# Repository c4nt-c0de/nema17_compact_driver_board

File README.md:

# Wi-Fi-Controlled Stepper Motor Driver Board

As part of an embedded programming coursework, I designed a custom compact Wi-Fi-controlled stepper motor driver board engineered to mount directly onto the back of a NEMA17 motor.

Before the design phase, we were required to submit an initial project proposal (this file is in the "study" folder). As always, there were some deviations from that plan due to unexpected challenges and poor decisions.

---

## Hardware Overview

* Microcontroller: ESP32-S2-MINI-2-N4
* Stepper Driver: TMC2209-LA-T (featuring UART interface for stallGuard and configuration)
* Shaft Encoder: AS5600-ASOT
* IR Receiver: IRM-H638T-TR2-TL
* Power Supply: 
  * Motor Power: RJ45 connector (testing whether a Cat5 cable can be used to supply power to the motor over a longer distance than a typical USB cable)
  * Logic Power: USB-C (5V) using a TPS54331DR switching regulator

---

## Board Renders & Layout

The biggest experiment in this project was attempting to place components on both sides of the PCB. At the time of design, JLCPCB did not offer double-sided PCBA services. While the cost today would likely deter me from this approach, I needed to populate both sides to fit the design onto the back of a NEMA17 motor.

I opted for a standard PCBA with components soldered to the top side, but the board was designed to be cut in half, with the two sections then glued together and soldered at specific points to create electrical connections.

The choice of an RJ45 connector for delivering power was also unconventional, but it was on hand and, by my calculations, could safely carry 24V at the expected currents.

### Top View

### Bottom View

### Front Layout

---

## Schematics & Subsystems

### Complete System Schematic

<br><br>
### Power Connector

<br><br>
### Switching Regulator (TPS54331DR)

<br><br>
### Stepper Driver (TMC2209)

<br><br>
### Shaft Encoder (AS5600)

<br><br>
### IR Receiver (IRM-H630T)

<br><br>
### External Crystal

---

## Firmware & Logic

The firmware runs on the ESP32-S2, handling:
1. Motor Control: Managed via stepper driver libraries (e.g., [TMCStepper](https://github.com/teemuatlut/TMCStepper)).
2. Position Tracking: Sampling PWM output from the AS5600 magnetic encoder.
3. Communication: Receiving motion commands over Wi-Fi via a simple web GUI and transmitting real-time shaft position and StallGuard values.

---

## Retrospective & Mistakes

This project would require a few more iterations to be considered a full success, but it was a significant learning experience. I improved my soldering skills by necessity, having to remove components and bridge pads with wire to correct design errors. I also hand-soldered the ESP32 module, something I had never done before, because JLCPCB was out of stock on the module I was already familiar with.

The motor successfully spun based on commands, counted steps, tracked shaft position, and returned StallGuard values. However, torque was limited and mechanical assembly was tedious.

* **Double-sided PCB:** Sticking together two PCBs seemed interesting, but caused many headaches. Even designing it in KiCad was far more difficult than expected, and the final assembly was tedious. I wouldn't repeat it unless absolutely necessary, though it does save space. If I ever attempt something similar, I should design the through-holes large enough to accommodate a typical Arduino pin that can be pushed through and soldered from both sides to create a crude via. My through-holes were too small, making it difficult for solder to flow into the tight spaces.

* **The Logic Voltage Drop:** A major oversight involved the reverse current protection on the 5V rail near the USB-C port. The diode introduced an excessive voltage drop that dragged the voltage too far below 5V when powered exclusively via USB-C, completely preventing the TMC2209 drivers from functioning until I physically bypassed the diode and shorted the pads. Consequently, I relied entirely on 5V from the USB port, which limited motor torque significantly.

Every mistake taught me far more about board bring-up and power distribution than a flawless design would have. Ultimately, I am satisfied with the result: I learned a great deal, completed an independent project, and passed the class.

## Photos of the Assembled Board
<div align="center">
  <table>
    <tr>
      <td align="center"><b>Corner View</b></td>
      <td align="center"><b>Top View</b></td>
    </tr>
    <tr>
      <td align="center" style="padding: 10px;">
        
      </td>
      <td align="center" style="padding: 10px;">
        
      </td>
    </tr>
  </table>
</div>

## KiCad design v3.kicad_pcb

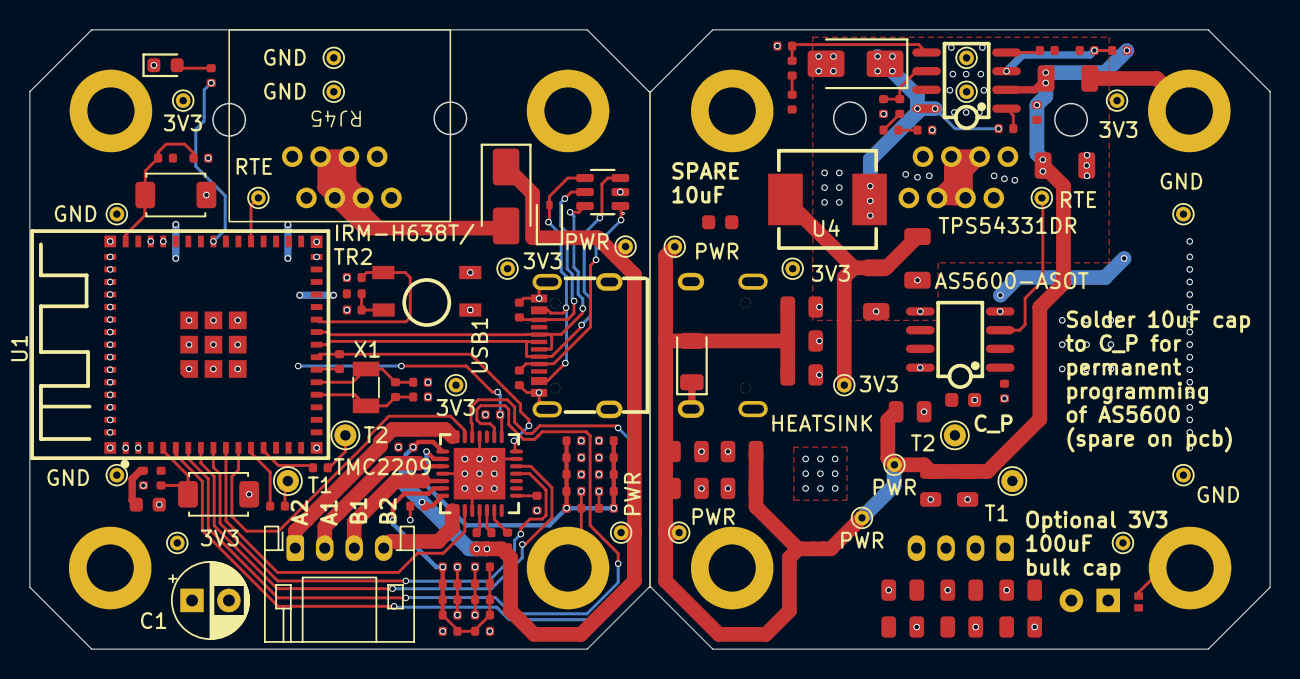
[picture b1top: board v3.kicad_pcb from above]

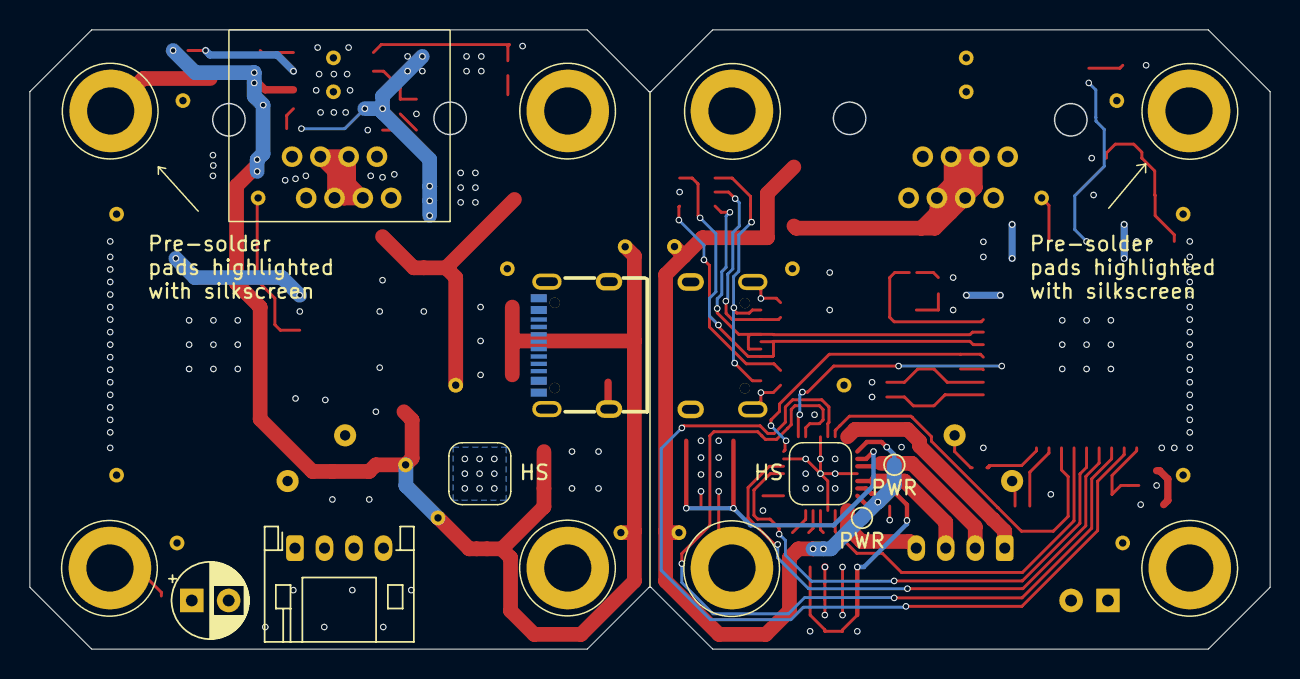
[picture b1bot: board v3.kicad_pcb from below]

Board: 2 copper layers, 84.1 x 42.0 mm, 140 parts (10 on the bottom side), 49 nets.

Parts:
BOOT1: Tactile Button, 160gf; SW_TS-1088-AR02016
C1, C1#2: C_Polarized; CP_Radial_D5.0mm_P2.50mm
C2, C4, C6, C7, C8, C9: 22uF; C_0805
C3: 22uF; C_0603
C5, C10, C11, C20, C25, C27, C28, C29: 100nF; C_0402
C12, C13: 10uF; C_0603
C14, C15: 4.7uF; C_1206
C16, C17: 10nF; C_0402
C18: 47pF; C_0402
C19: 1nF; C_0402
C21, C22: 47uF; C_1206
C23: 4.7uF; C_0402
C24: 2.2uF; C_0402
C26: 22nF; C_0402
C30, C31, C32, C33, C34, C35, C36, C37, C38, C39: 10uF; C_0805
C40, C41: 12pF; C_0402
CGQ1: IRM-H638T/TR2; SENSOR-SMD_IRM-H638T-TR2-TL
D1: SRV05-4_C7420376; SOT-23-6_L2.9-W1.6-P0.95-LS2.8-BL-1
D2: 1N5819WS; D_SOD-323
D3: SS54; D_SMA
D4: Red; D_0603
D5: SMF24CA; D_SOD-123FL
D6: H3V3L10B; D_DFN1006-2L
D7: SSL34; D_SMA
H1, H1#2, H2, H2#2, H3, H3#2, H4, H4#2: MountingHole_Pad; MountingHole_3.2mm_M3_DIN965_Pad
J1, J1#2: RJ45; RJ45_home
J2, J2#2: Conn_01x04_Socket; JST_PH_S4B-PH-K_1x04_P2.00mm_Horizontal
R1, R2: 5.1kΩ; R_0402
R3, R8, R14: 10kΩ; R_0402
R4, R5, R6: 1kΩ; R_0402
R7: 330Ω; R_0402
R9: 330kΩ; R_0402
R10, R16: 100kΩ; R_0402
R11: 2.4kΩ; R_0402
R12: 27kΩ; R_0402
R13: 3.3kΩ; R_0402
R15: 0Ω; R_0402
R17: 100Ω; R_0402
R18, R19, R20, R21, R22, R23, R24, R25, R26, R27, R28, R29, R30, R31, R32, R33, R34, R35, R36, R37: 1Ω; R_0402
R38: 1MΩ; R_0402
RST1: Tactile Button, 160gf; SW_TS-1088-AR02016
TP1, TP1#2, TP2, TP2#2, TP3, TP3#3, TP4#2, TP4#3: GND; TestPoint_THTPad_D1.0mm_Drill0.5mm
TP2#3, TP6, TP6#3, TP6#4, TP7#2, TP8: PWR; TestPoint_THTPad_D1.0mm_Drill0.5mm
TP3#2, TP5: T1; TestPoint_THTPad_D1.5mm_Drill0.7mm
TP4, TP6#2: T2; TestPoint_THTPad_D1.5mm_Drill0.7mm
TP7, TP10#2: RTE; TestPoint_THTPad_D1.0mm_Drill0.5mm
TP9, TP11#2: PWR; TestPoint_Pad_D1.0mm
TP10, TP11, TP12, TP12#2, TP13, TP13#2, TP14, TP15: 3V3; TestPoint_THTPad_D1.0mm_Drill0.5mm
U1: 2.4GHz; ESP32-S2-MINI-2-N4
U2: AS5600-ASOT; SOIC-8_L5.0-W4.0-P1.27-LS6.0-BL
U3: TPS54331DR; SOIC-8_L5.0-W4.0-P1.27-LS6.0-BL
U4: CYA0630-6.8UH; IND-SMD_L7.2-W6.6_GPSR0730
U5: TMC2209-LA-T; QFN-28_L5.0-W5.0-P0.50-BL-EP
USB1, USB1#2: TYPE-C 16PIN 2MD(073); USB-C-SMD_TYPE-C-6PIN-2MD-073
X1: Q13FC1350000400; Crystal_SMD_3215-2Pin_3.2x1.5mm

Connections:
3V3: C1.1, C1#2.1, C2.2, C3.1, C4.2, C5.2, C6.2, C7.2, C8.2, C9.2, C11.1, C12.1, C21.1, C22.1, C28.1, D6.2, R3.1, R8.1, R15.2, R17.2, TP10.1, TP11.1, TP12.1, TP12#2.1, TP13.1, TP13#2.1, TP14.1, TP15.1, U1.3 (3V3), U2.1 (VDD5V), U2.2 (VDD3V3), U4.2, U5.15 (VCC_IO)
5V: D1.4 (I/O), D2.2, USB1.2 (VBUS), USB1.11 (VBUS)
24V: D3.2, J1.3, J1.4, J1.5, J1.6, J1#2.3, J1#2.4, J1#2.5, J1#2.6
/CC1: D1.1 (I/O), R2.2, USB1.4 (CC1)
/CC2: D1.5 (VP), R1.2, USB1.10 (CC2)
/D+: D1.6 (I/O), U1.24 (IO20), USB1.6 (DP1), USB1.8 (DP2)
/D-: D1.3 (I/O), U1.23 (IO19), USB1.5 (DN2), USB1.7 (DN1)
/GPIO1: U1.5 (IO1), U5.19 (DIR)
/GPIO2: U1.6 (IO2), U5.16 (STEP)
/GPIO3: U1.7 (IO3), U5.12 (INDEX)
/GPIO4: U1.8 (IO4), U5.11 (DIAG)
/GPIO5: U1.9 (IO5), U5.2 (ENN)
/GPIO6: U1.10 (IO6), U5.20 (STDBY)
/GPIO7: R4.2, TP3#2.1, U1.11 (IO7)
/GPIO8: R5.2, TP4.1, U1.12 (IO8)
/GPIO21: CGQ1.3 (VOUT), R16.2, U1.25 (IO21)
/GPIO39: TP7.1, TP10#2.1, U1.35 (IO39), U2.3 (OUT)
/GPIO42: R7.1, U1.38 (IO42)
/PDN_UART: R6.1, U1.22 (IO18), U5.14 (PDN_UART)
/RX1: R6.2, U1.21 (IO17)
/extern_crystal/1: C40.1, R38.1, U1.19 (IO15), X1.1
/extern_crystal/2: C41.1, R38.2, U1.20 (IO16), X1.2
/stepper_driver_tmc2209/OA1: J2.2, J2#2.2, U5.24 (OA1)
/stepper_driver_tmc2209/OA2: J2.1, J2#2.1, U5.21 (OA2)
/stepper_driver_tmc2209/OB1: J2.3, J2#2.3, U5.26 (OB1)
/stepper_driver_tmc2209/OB2: J2.4, J2#2.4, U5.1 (OB2)
GND: BOOT1.1 (A), C1.2, C1#2.2, C2.1, C3.2, C4.1, C5.1, C6.1, C7.1, C8.1, C9.1, C10.1, C11.2, C12.2, C14.2, C15.2, C16.2, C17.2, C18.2, C21.2, C22.2, C23.1, C24.1, C27.2, C28.2, C29.1, C30.1, C31.1, C32.1, C33.1, C34.1, C35.1, C36.1, C37.1, C38.1, C39.1, C40.2, C41.2, CGQ1.1 (GND), CGQ1.2 (GND), D1.2 (VN), D4.1, D5.1, D6.1, D7.2, H1.1, H1#2.1, H2.1, H2#2.1, H3.1, H3#2.1, H4.1, H4#2.1, J1.1, J1.2, J1.7, J1.8, J1#2.1, J1#2.2, J1#2.7, J1#2.8, R1.1, R2.1, R10.2, R12.2, R13.2, R16.1, R18.2, R19.2, R20.2, R21.2, R22.2, R23.2, R24.2, R25.2, R26.2, R27.2, R28.2, R29.2, R30.2, R31.2, R32.2, R33.2, R34.2, R35.2, R36.2, R37.2, RST1.1 (A), TP1.1, TP1#2.1, TP2.1, TP2#2.1, TP3.1, TP3#3.1, TP4#2.1, TP4#3.1, U1.1 (GND), U1.2 (GND), U1.30 (GND), U1.42 (GND), U1.43 (GND), U1.46 (GND), U1.47 (GND), U1.48 (GND), U1.49 (GND), U1.50 (GND), U1.51 (GND), U1.52 (GND), U1.53 (GND), U1.54 (GND), U1.55 (GND), U1.56 (GND), U1.57 (GND), U1.58 (GND), U1.59 (GND), U1.60 (GND), U1.61 (GND), U1.62 (GND), U1.63 (GND), U1.64 (GND), U1.65 (GND), U2.4 (GND), U2.5 (PGO), U2.8 (DIR), U3.7 (GND), U5.3 (GND), U5.13 (CLK), U5.18 (GND), U5.25 (UNUSED), U5.29 (EP), USB1.1 (GND), USB1.12 (GND), USB1.13 (SHELL), USB1.14 (SHELL), USB1#2.1 (GND), USB1#2.2 (VBUS), USB1#2.3 (SBU2), USB1#2.4 (CC1), USB1#2.5 (DN2), USB1#2.6 (DP1), USB1#2.7 (DN1), USB1#2.8 (DP2), USB1#2.9 (SBU1), USB1#2.10 (CC2), USB1#2.11 (VBUS), USB1#2.12 (GND), USB1#2.13 (SHELL), USB1#2.14 (SHELL)
unnamed: BOOT1.2 (B), R3.2, U1.4 (IO0)
unnamed: C19.2, R11.1
unnamed: C23.2, CGQ1.4 (VCC), R17.1
unnamed: D4.2, R7.2
unnamed: R4.1, TP5.1
unnamed: R5.1, TP6#2.1
unnamed: R11.2, R12.1
unnamed: R14.2, R15.1
unnamed: C10.2, R8.2, RST1.2 (B), U1.45 (EN)
unnamed: C20.2, U3.1 (BOOT)
unnamed: C18.1, C19.1, U3.6 (COMP)
unnamed: R9.2, R10.1, U3.3 (EN)
unnamed: C20.1, D7.1, U3.8 (PH), U4.1
unnamed: C17.1, U3.4 (SS)
unnamed: R13.1, R14.1, U3.5 (VSENSE)
unnamed: C24.2, U5.8 (5VOUT)
unnamed: R19.1, R21.1, R23.1, R25.1, R27.1, R29.1, R31.1, R33.1, R35.1, R37.1, U5.23 (BRA)
unnamed: R18.1, R20.1, R22.1, R24.1, R26.1, R28.1, R30.1, R32.1, R34.1, R36.1, U5.27 (BRB)
unnamed: C26.1, U5.5 (CPI)
unnamed: C26.2, U5.4 (CPO)
unnamed: C25.2, U5.6 (VCP)
POWERLANE: C14.1, C15.1, C16.1, C25.1, C27.1, C29.2, C30.2, C31.2, C32.2, C33.2, C34.2, C35.2, C36.2, C37.2, C38.2, C39.2, D2.1, D3.1, D5.2, R9.1, TP2#3.1, TP6.1, TP6#3.1, TP6#4.1, TP7#2.1, TP8.1, TP9.1, TP11#2.1, U3.2 (VIN), U5.22 (VS), U5.28 (VS)

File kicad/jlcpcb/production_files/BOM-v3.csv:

Comment,Designator,Footprint,LCSC,Quantity
0Ω,R15,R_0402,C17168,1
100kΩ,"R10,R16",R_0402,C25741,2
100nF,"C25,C27,C28,C29",C_0402,C1525,4
100nF,"C10,C11,C20,C5",C_0402,C307331,4
100Ω,R17,R_0402,C25076,1
10kΩ,"R14,R3,R8",R_0402,C25744,3
10nF,"C16,C17",C_0402,C15195,2
10uF,C13,C_0603,C19702,1
10uF,"C30,C31,C32,C33,C34,C35,C36,C37,C38,C39",C_0805,C440198,10
12pF,"C40,C41",C_0402,C1547,2
1MΩ,R38,R_0402,C26083,1
1N5819WS,D2,D_SOD-323,C191023,1
1kΩ,"R4,R5,R6",R_0402,C11702,3
1nF,C19,C_0402,C1523,1
1Ω,"R18,R19,R20,R21,R22,R23,R24,R25,R26,R27,R28,R29,R30,R31,R32,R33,R34,R35,R36,R37",R_0402,C25086,20
2.2uF,C24,C_0402,C12530,1
2.4GHz,U1,ESP32-S2-MINI-2-N4,C3013906,1
2.4kΩ,R11,R_0402,C25882,1
22nF,C26,C_0402,C1532,1
22uF,"C2,C4,C6,C7,C8,C9",C_0805,C45783,6
22uF,C3,C_0603,C59461,1
27kΩ,R12,R_0402,C25771,1
3.3kΩ,R13,R_0402,C25890,1
330kΩ,R9,R_0402,C25778,1
330Ω,R7,R_0402,C25104,1
4.7uF,C23,C_0402,C23733,1
4.7uF,"C14,C15",C_1206,C29823,2
47pF,C18,C_0402,C1567,1
47uF,"C21,C22",C_1206,C96123,2
5.1kΩ,"R1,R2",R_0402,C25905,2
AS5600-ASOT,U2,SOIC-8_L5.0-W4.0-P1.27-LS6.0-BL,C499458,1
CYA0630-6.8UH,U4,IND-SMD_L7.2-W6.6_GPSR0730,C5189749,1
H3V3L10B,D6,D_DFN1006-2L,C20615781,1
IRM-H638T/TR2,CGQ1,SENSOR-SMD_IRM-H638T-TR2-TL,C91447,1
Q13FC1350000400,X1,Crystal_SMD_3215-2Pin_3.2x1.5mm,C32346,1
Red,D4,D_0603,C2286,1
SMF24CA,D5,D_SOD-123FL,C19077515,1
SRV05-4_C7420376,D1,SOT-23-6_L2.9-W1.6-P0.95-LS2.8-BL-1,C7420376,1
SS54,D3,D_SMA,C22452,1
SSL34,D7,D_SMA,C41410771,1
TMC2209-LA-T,U5,QFN-28_L5.0-W5.0-P0.50-BL-EP,C2150710,1
TPS54331DR,U3,SOIC-8_L5.0-W4.0-P1.27-LS6.0-BL,C9865,1
TYPE-C 16PIN 2MD(073),USB1,USB-C-SMD_TYPE-C-6PIN-2MD-073,C2765186,1
"Tactile Button, 160gf","BOOT1,RST1",SW_TS-1088-AR02016,C720477,2
PWR,TP6,TestPoint_THTPad_D1.0mm_Drill0.5mm,,1
GND,TP4,TestPoint_THTPad_D1.0mm_Drill0.5mm,,1
RTE,TP10,TestPoint_THTPad_D1.0mm_Drill0.5mm,,1
GND,TP3,TestPoint_THTPad_D1.0mm_Drill0.5mm,,1
GND,TP1,TestPoint_THTPad_D1.0mm_Drill0.5mm,,1
PWR,TP11,TestPoint_Pad_D1.0mm,,1
RJ45,J1,RJ45_home,,1
Conn_01x04_Socket,,JST_PH_S4B-PH-K_1x04_P2.00mm_Horizontal,,0
PWR,TP7,TestPoint_THTPad_D1.0mm_Drill0.5mm,,1
3V3,TP13,TestPoint_THTPad_D1.0mm_Drill0.5mm,,1
PWR,TP2,TestPoint_THTPad_D1.0mm_Drill0.5mm,,1
3V3,TP12,TestPoint_THTPad_D1.0mm_Drill0.5mm,,1
T1,TP5,TestPoint_THTPad_D1.5mm_Drill0.7mm,,1
PWR,TP8,TestPoint_THTPad_D1.0mm_Drill0.5mm,,1
PWR,TP9,TestPoint_Pad_D1.0mm,,1
3V3,TP14,TestPoint_THTPad_D1.0mm_Drill0.5mm,,1
3V3,TP15,TestPoint_THTPad_D1.0mm_Drill0.5mm,,1

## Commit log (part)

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2025-12-30 Motor ACTUALLY SPINS !!!!!!!
